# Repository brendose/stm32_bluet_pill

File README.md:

<h1 align="center">Welcome to Project: stm32_bluet_pill </br> (a Bluetooth OSHW design) </h1>
<div align="center">

<a href="#introduction">Introduction</a> &nbsp;&bull;&nbsp;
<a href="#directory">Directory</a> &nbsp;&bull;&nbsp;
<a href="#documentation">Documentation</a> &nbsp;&bull;&nbsp;
<a href="#notes">Notes</a>
</div>

# Introduction
The <b>stm32_bluet_pill</b> project is a 'breadboardable' 1.8V IO STM32WB55 Bluetooth Module with battery charging. 
The purpose of this project is to provide a development platform for wearables. The board contains:

- ST Microelectronics STM32WB55
- 32Mbit QSPI Flash
- Texas Instruments BQ25185 battery charger
- PCB Antenna with U.FL switch connector 
- 2x 15 pin GPIO headers
- Tag-Connect JTAG connector 
- USB-C connector
- 3-Pin Battery connector
- Charge Status and Bluetooth Connection indicator LEDs

## Directory

### Projects top-level directory

    .
    ├── bom                     # stm32_blue_pill iBOM
    ├── docs                    # Documentation files (alternatively `doc`)
    ├── images                  # Images used on this GitHub page
    ├── schematics              # Schematics of the stm32_bluet_pill
    ├── step                    # 3D STEP model of the design
    ├── tapeout                 # Gerbers, Drill Drawings and other output files for PCB Fab and Assembly
    └── README.md

## Documentation

### Block Diagram
<div align="center">

</div>

## Notes

This repository is not actively maintained, so if you spot any bugs, please <a href="https://github.com/brendose/stm32_bluet_pill/issues/new">raise an issue</a> and I will try get to it.

This is not an officially supported Google product.

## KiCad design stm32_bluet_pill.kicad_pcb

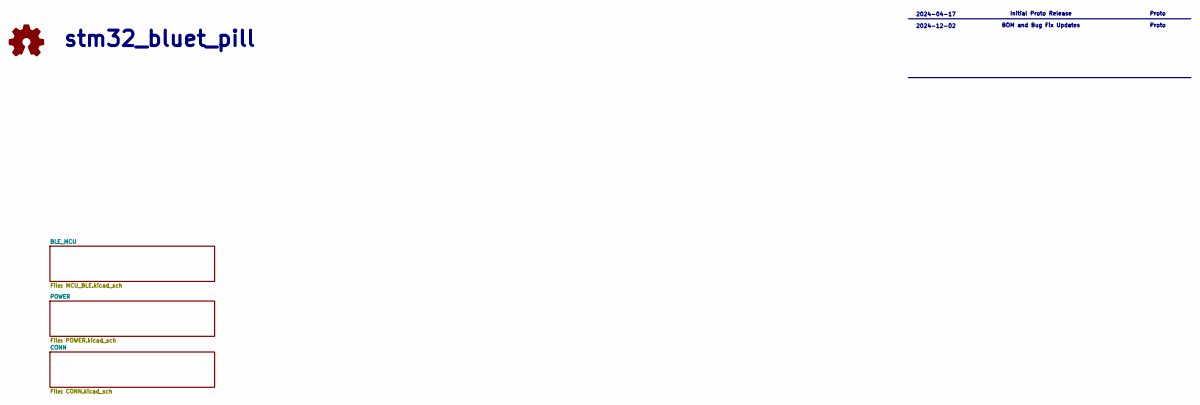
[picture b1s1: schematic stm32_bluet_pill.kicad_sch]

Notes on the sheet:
Proto
2024-04-17
${TITLE}
Initial Proto Release
BOM and Bug Fix Updates
2024-12-02

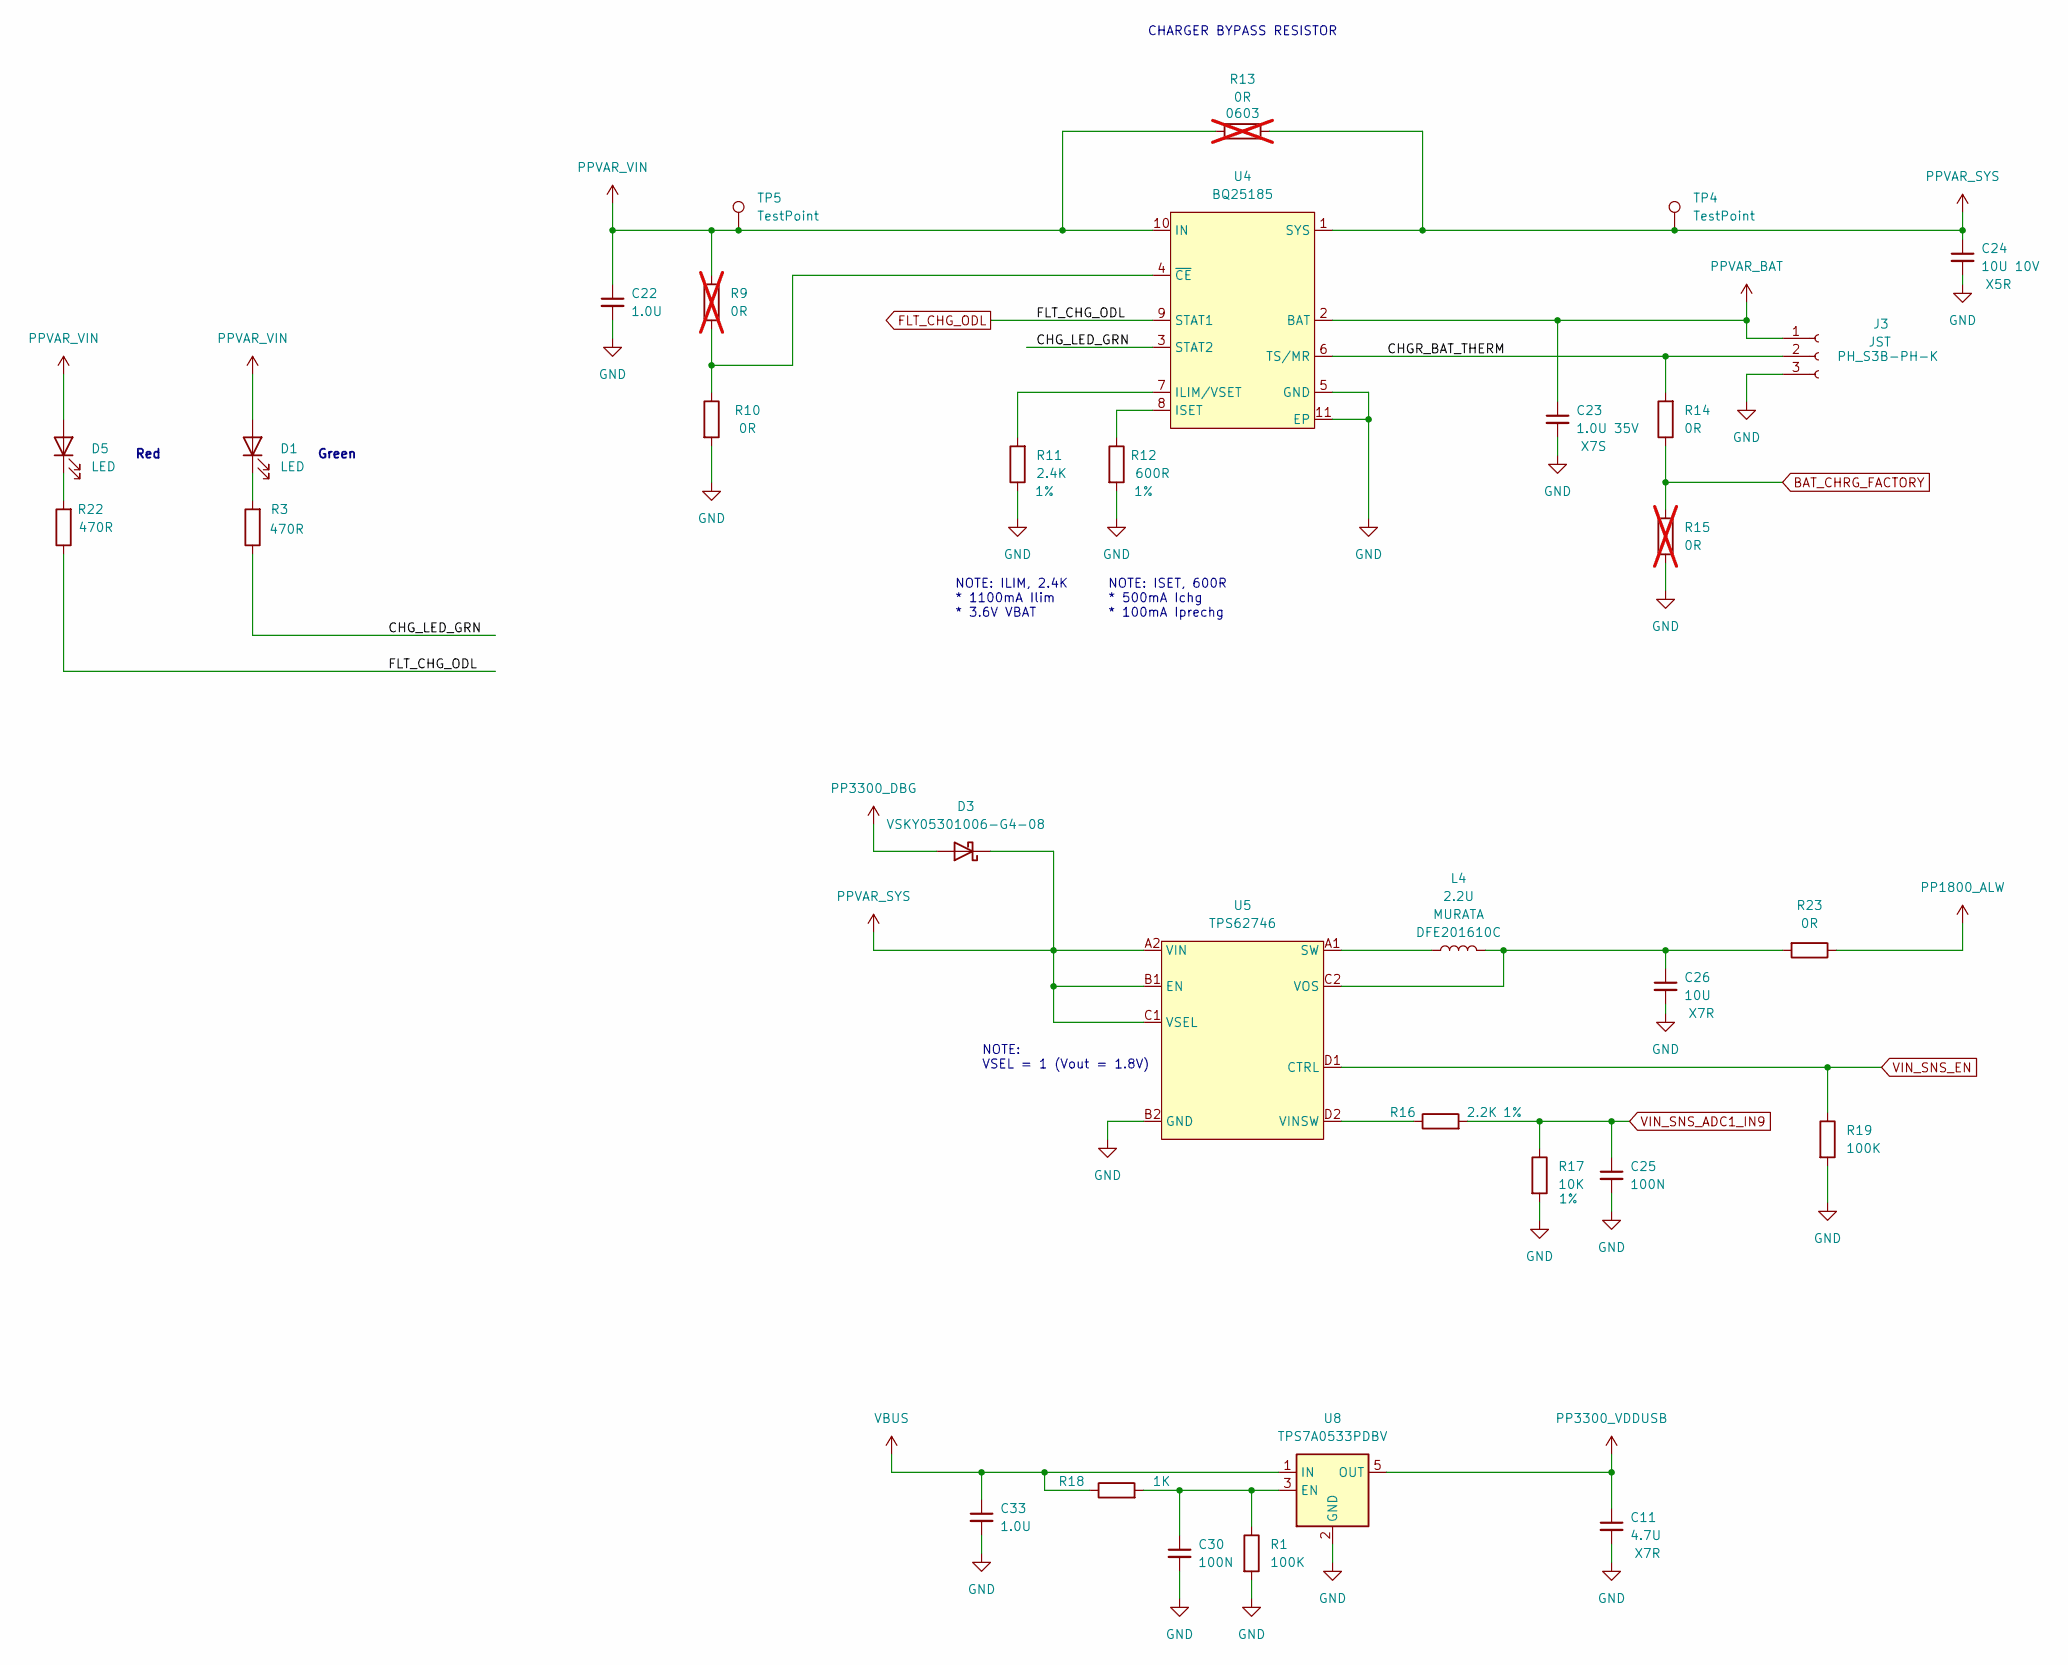
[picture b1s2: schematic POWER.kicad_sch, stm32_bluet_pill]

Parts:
C11: 4.7U; C_0402_1005Metric; MFG_PN GRM155R60J106ME11
C22, C33: 1.0U; C_0402_1005Metric
C23: 1.0U 35V; C_0402_1005Metric; MFR_PN C1005JB1V105K050BC
C24: 10U 10V; C_0402_1005Metric; MFR_PN CL05A106MP8NUB8
C25, C30: 100N; C_0201_0603Metric
C26: 10U; C_0402_1005Metric; MFG_PN GRM155R60J106ME11
D1, D5: LED; D_0402_1005Metric
D3: VSKY05301006-G4-08; D_0402_1005Metric
J3: PH_S3B-PH-K; JST_PH_S3B-PH-K_1x03_P2.00mm_Horizontal; MFG_PN PH_S3B-PH-K
L4: 2.2U; L_Murata_DFE201610P; MFG_PN DFE201610C
R1, R19: 100K; R_0201_0603Metric
R3, R22: 470R; R_0201_0603Metric
R9, R15: 0R; R_0201_0603Metric; not fitted
R10, R14: 0R; R_0201_0603Metric
R11: 2.4K; R_0201_0603Metric
R12: 600R; R_0201_0603Metric
R13: 0R; R_0603_1608Metric; not fitted
R16: 2.2K; R_0201_0603Metric
R17: 10K; R_0201_0603Metric
R18: 1K; R_0201_0603Metric
R23: 0R; R_0402_1005Metric
TP4, TP5: TestPoint; TestPoint_Pad_D1.0mm
U4: BQ25185; Texas_DLH_WSON-10
U5: TPS62746; Texas_DSBGA-8_0.705x1.468mm_Layout2x4_P0.4mm
U8: TPS7A0533PDBV; SOT-23-5

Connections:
/POWER/CHGR_BAT_THERM: J3.2, R14.2, U4.6 (TS/MR)
/POWER/CHG_LED_GRN: R3.1, U4.3 (STAT2)
BAT_CHRG_FACTORY: R14.1, R15.2; also elsewhere on the board
FLT_CHG_ODL: R22.1, U4.9 (STAT1); also elsewhere on the board
GND: C11.2, C22.2, C23.2, C24.2, C25.2, C26.2, C30.2, C33.2, J3.3, R1.2, R10.2, R11.1, R12.2, R15.1, R17.2, R19.2, U4.5 (GND), U4.11 (EP), U5.B2 (GND), U8.2 (GND); also elsewhere on the board
unnamed: D1.1 (K), R3.2
unnamed: D5.1 (K), R22.2
unnamed: R11.2, U4.7 (ILIM/VSET)
unnamed: R12.1, U4.8 (ISET)
unnamed: R9.1, R10.1, U4.4 (~CE)
unnamed: L4.1, U5.A1 (SW)
unnamed: R16.1, U5.D2 (VINSW)
unnamed: C26.1, L4.2, R23.2, U5.C2 (VOS)
unnamed: C30.1, R1.1, R18.2, U8.3 (EN)
PP1800_ALW: R23.1; also elsewhere on the board
PP3300_DBG: D3.2 (A); also elsewhere on the board
PP3300_VDDUSB: C11.1, U8.5 (OUT); also elsewhere on the board
PPVAR_BAT: C23.1, J3.1, U4.2 (BAT)
PPVAR_SYS: C24.1, D3.1 (K), R13.1, TP4.1, U4.1 (SYS), U5.A2 (VIN), U5.B1 (EN), U5.C1 (VSEL)
PPVAR_VIN: C22.1, D1.2 (A), D5.2 (A), R9.2, R13.2, TP5.1, U4.10 (IN); also elsewhere on the board
VBUS: C33.1, R18.1, U8.1 (IN); also elsewhere on the board
VIN_SNS_ADC1_IN9: C25.1, R16.2, R17.1; also elsewhere on the board
VIN_SNS_EN: R19.1, U5.D1 (CTRL); also elsewhere on the board

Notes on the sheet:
CHARGER BYPASS RESISTOR
NOTE: ILIM, 2.4K * 1100mA Ilim * 3.6V VBAT
NOTE: VSEL = 1 (Vout = 1.8V)
Red
NOTE: ISET, 600R * 500mA Ichg * 100mA Iprechg
Green

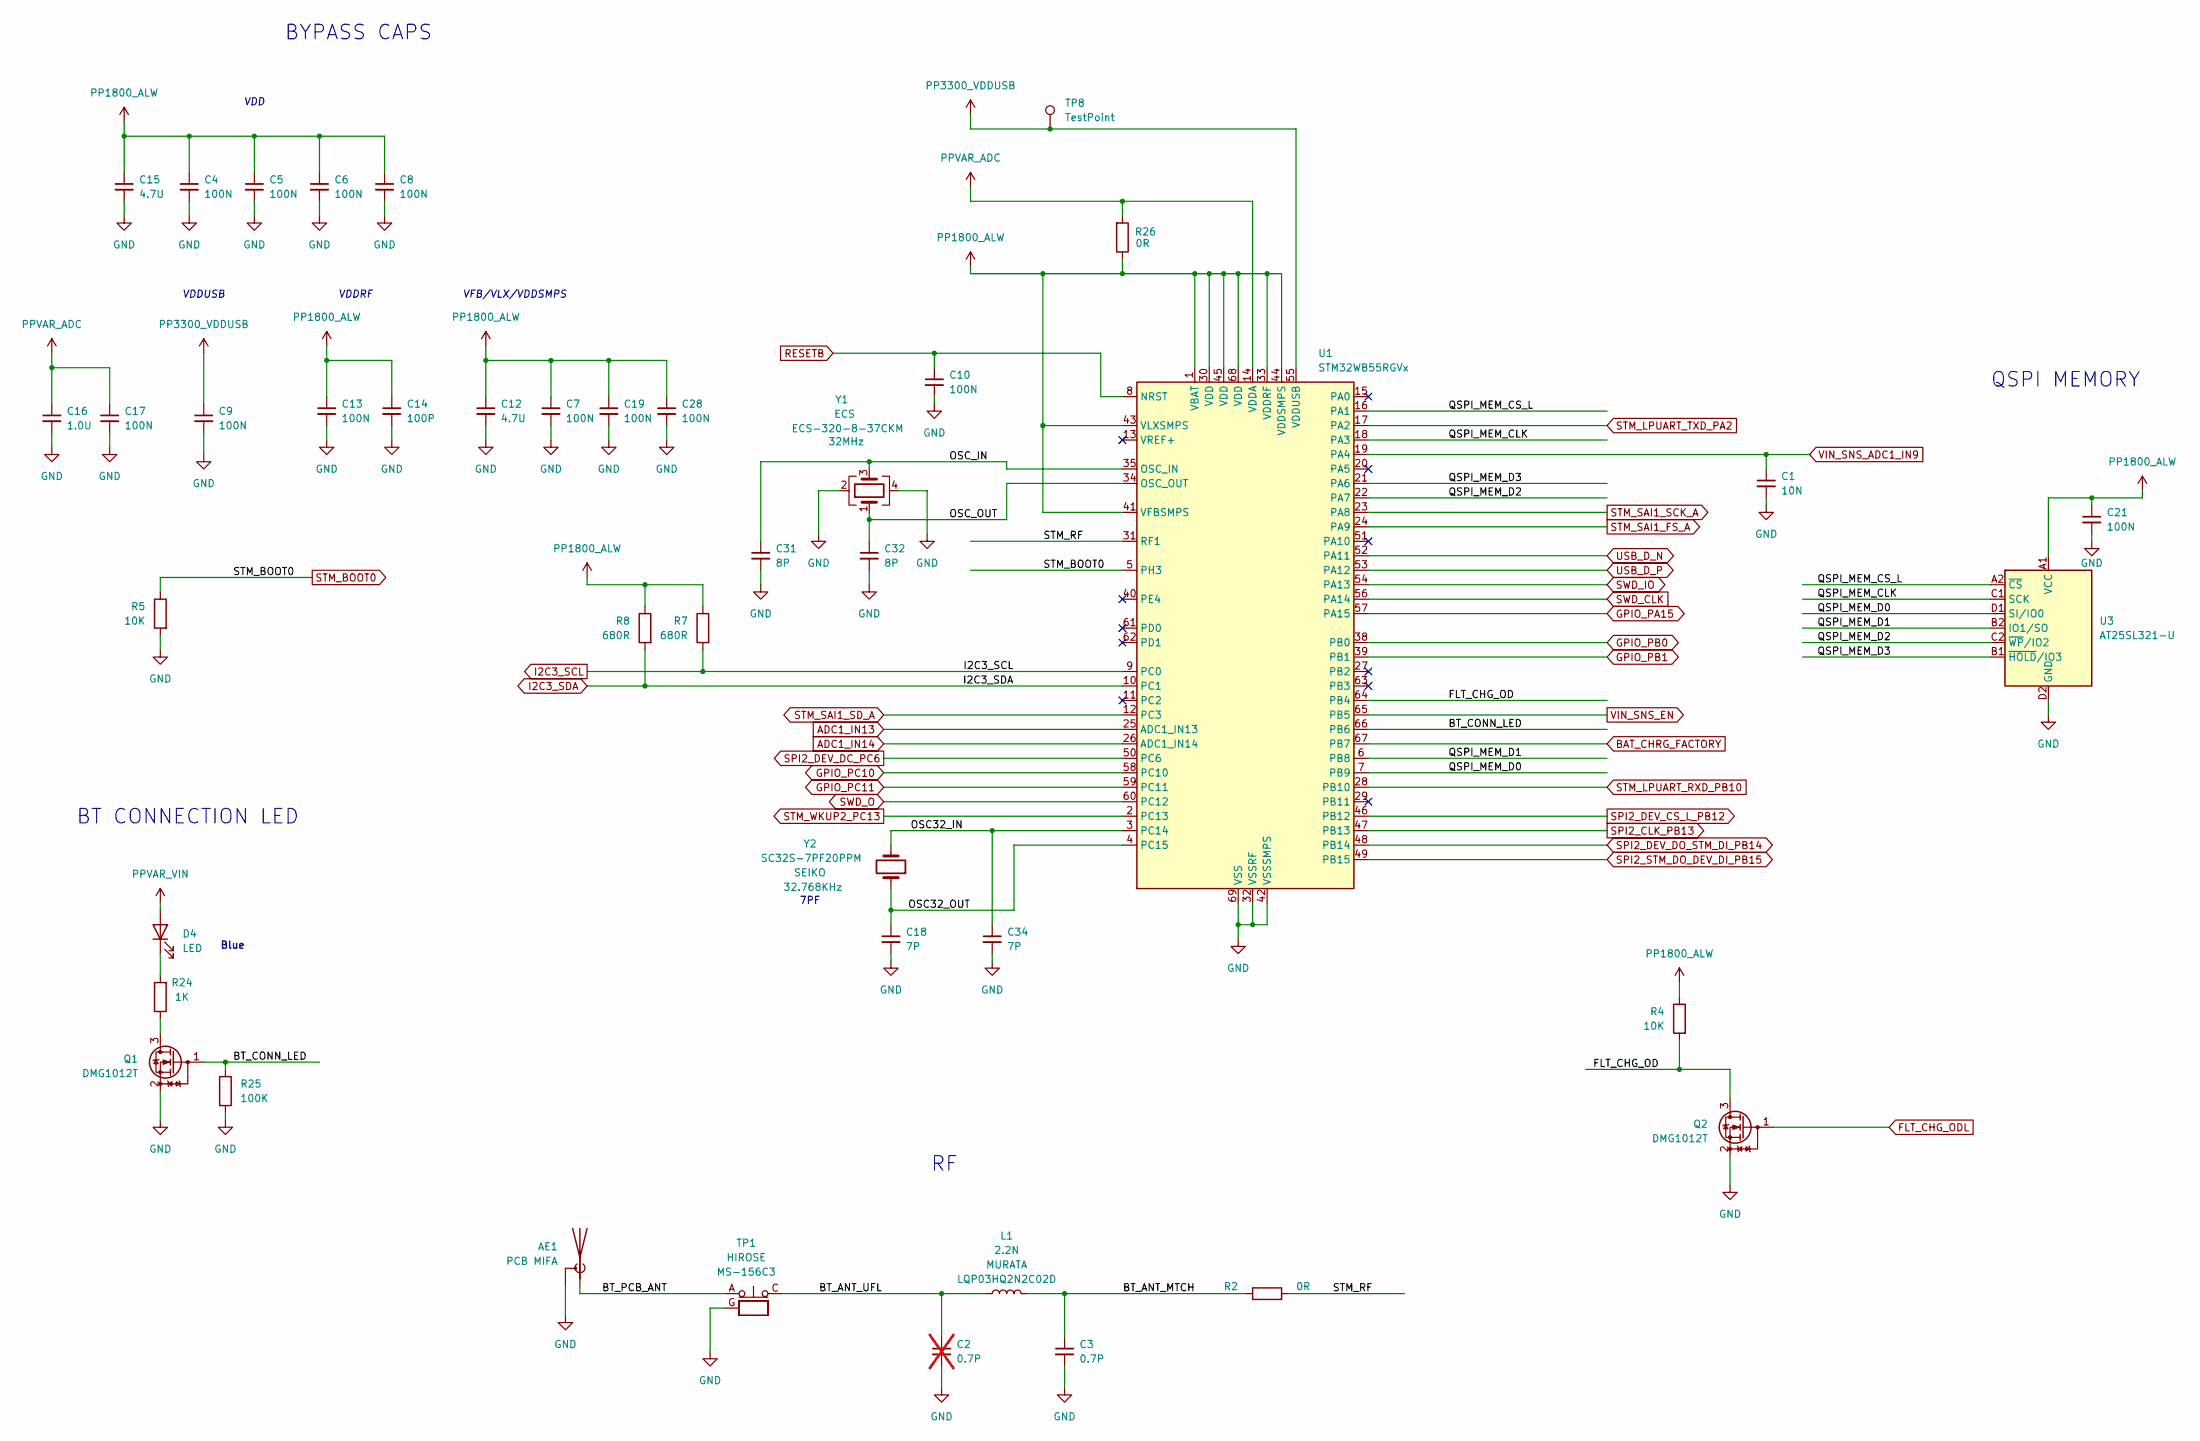
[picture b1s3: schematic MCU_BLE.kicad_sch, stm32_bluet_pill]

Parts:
AE1: PCB MIFA; Texas_SWRA117D_2.4GHz_Right
C1: 10N; C_0201_0603Metric
C2: 0.7P; C_0201_0603Metric; not fitted
C3: 0.7P; C_0201_0603Metric
C4, C5, C6, C7, C8, C9, C10, C13, C17, C19, C21, C28: 100N; C_0201_0603Metric
C12, C15: 4.7U; C_0402_1005Metric
C14: 100P; C_0201_0603Metric
C16: 1.0U; C_0201_0603Metric
C18, C34: 7P; C_0201_0603Metric
C31, C32: 8P; C_0201_0603Metric
D4: LED; D_0402_1005Metric
L1: 2.2N; D_0201_0603Metric; MFG_PN LQP03HQ2N2C02D
Q1, Q2: DMG1012T; SOT-523
R2: 0R; R_0201_0603Metric
R4, R5: 10K; R_0201_0603Metric
R7, R8: 680R; R_0201_0603Metric
R24: 1K; R_0201_0603Metric
R25: 100K; R_0201_0603Metric
R26: 0R; R_0402_1005Metric
TP1: MS-156C3; CoaxialSwitch_Hirose_MS-156C3_Horizontal; MFG_PN MS-156C3
TP8: TestPoint; TestPoint_Pad_D1.0mm
U1: STM32WB55RGVx; QFN-68-1EP_8x8mm_P0.4mm_EP6.4x6.4mm
U3: AT25SL321-U; WLCSP-8_1.551x2.284mm_P0.5mm
Y1: ECS-320-8-37CKM; Crystal_SMD_2016-4Pin_2.0x1.6mm; MFG_PN ECS-320-8-37CKM
Y2: SC32S-7PF20PPM; Crystal_SMD_3215-2Pin_3.2x1.5mm; MFG_PN SC32S-7PF20PPM

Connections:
/BLE_MCU/BT_ANT_MTCH: C3.1, L1.2, R2.1
/BLE_MCU/BT_ANT_UFL: C2.1, L1.1, TP1.C
/BLE_MCU/BT_CONN_LED: Q1.1 (G), R25.1, U1.66 (PB6)
/BLE_MCU/BT_PCB_ANT: AE1.1 (A), TP1.A
/BLE_MCU/FLT_CHG_OD: Q2.3 (D), R4.2, U1.64 (PB4)
/BLE_MCU/OSC32_IN: C34.1, U1.3 (PC14), Y2.2
/BLE_MCU/OSC32_OUT: C18.1, U1.4 (PC15), Y2.1
/BLE_MCU/OSC_IN: C31.1, U1.35 (OSC_IN), Y1.3
/BLE_MCU/OSC_OUT: C32.1, U1.34 (OSC_OUT), Y1.1
/BLE_MCU/QSPI_MEM_CLK: U1.18 (PA3), U3.C1 (SCK)
/BLE_MCU/QSPI_MEM_CS_L: U1.16 (PA1), U3.A2 (~CS)
/BLE_MCU/QSPI_MEM_D0: U1.7 (PB9), U3.D1 (SI/IO0)
/BLE_MCU/QSPI_MEM_D1: U1.6 (PB8), U3.B2 (IO1/SO)
/BLE_MCU/QSPI_MEM_D2: U1.22 (PA7), U3.C2 (~WP/IO2)
/BLE_MCU/QSPI_MEM_D3: U1.21 (PA6), U3.B1 (~HOLD/IO3)
/BLE_MCU/STM_RF: R2.2, U1.31 (RF1)
ADC1_IN13: U1.25 (ADC1_IN13); also elsewhere on the board
ADC1_IN14: U1.26 (ADC1_IN14); also elsewhere on the board
BAT_CHRG_FACTORY: U1.67 (PB7); also elsewhere on the board
FLT_CHG_ODL: Q2.1 (G); also elsewhere on the board
GND: AE1.2 (Shield), C1.2, C2.2, C3.2, C4.2, C5.2, C6.2, C7.2, C8.2, C9.2, C10.2, C12.2, C13.2, C14.2, C15.2, C16.2, C17.2, C18.2, C19.2, C21.2, C28.2, C31.2, C32.2, C34.2, Q1.2 (S), Q2.2 (S), R5.2, R25.2, TP1.G, U1.32 (VSSRF), U1.42 (VSSSMPS), U1.69 (VSS), U3.D2 (GND), Y1.2, Y1.4; also elsewhere on the board
GPIO_PA15: U1.57 (PA15); also elsewhere on the board
GPIO_PB0: U1.38 (PB0); also elsewhere on the board
GPIO_PB1: U1.39 (PB1); also elsewhere on the board
GPIO_PC10: U1.58 (PC10); also elsewhere on the board
GPIO_PC11: U1.59 (PC11); also elsewhere on the board
I2C3_SCL: R7.2, U1.9 (PC0); also elsewhere on the board
I2C3_SDA: R8.2, U1.10 (PC1); also elsewhere on the board
unnamed: D4.1 (K), R24.2
unnamed: Q1.3 (D), R24.1
PP1800_ALW: C4.1, C5.1, C6.1, C7.1, C8.1, C12.1, C13.1, C14.1, C15.1, C19.1, C21.1, C28.1, R4.1, R7.1, R8.1, R26.1, U1.1 (VBAT), U1.30 (VDD), U1.33 (VDDRF), U1.41 (VFBSMPS), U1.43 (VLXSMPS), U1.44 (VDDSMPS), U1.45 (VDD), U1.68 (VDD), U3.A1 (VCC); also elsewhere on the board
PP3300_VDDUSB: C9.1, TP8.1, U1.55 (VDDUSB); also elsewhere on the board
PPVAR_ADC: C16.1, C17.1, R26.2, U1.14 (VDDA); also elsewhere on the board
PPVAR_VIN: D4.2 (A); also elsewhere on the board
RESETB: C10.1, U1.8 (NRST); also elsewhere on the board
SPI2_CLK_PB13: U1.47 (PB13); also elsewhere on the board
SPI2_DEV_CS_L_PB12: U1.46 (PB12); also elsewhere on the board
SPI2_DEV_DC_PC6: U1.50 (PC6); also elsewhere on the board
SPI2_DEV_DO_STM_DI_PB14: U1.48 (PB14); also elsewhere on the board
SPI2_STM_DO_DEV_DI_PB15: U1.49 (PB15); also elsewhere on the board
STM_BOOT0: R5.1, U1.5 (PH3); also elsewhere on the board
STM_LPUART_RXD_PB10: U1.28 (PB10); also elsewhere on the board
STM_LPUART_TXD_PA2: U1.17 (PA2); also elsewhere on the board
STM_SAI1_FS_A: U1.24 (PA9); also elsewhere on the board
STM_SAI1_SCK_A: U1.23 (PA8); also elsewhere on the board
STM_SAI1_SD_A: U1.12 (PC3); also elsewhere on the board
STM_WKUP2_PC13: U1.2 (PC13); also elsewhere on the board
SWD_CLK: U1.56 (PA14); also elsewhere on the board
SWD_IO: U1.54 (PA13); also elsewhere on the board
SWD_O: U1.60 (PC12); also elsewhere on the board
USB_D_N: U1.52 (PA11); also elsewhere on the board
USB_D_P: U1.53 (PA12); also elsewhere on the board
VIN_SNS_ADC1_IN9: C1.1, U1.19 (PA4); also elsewhere on the board
VIN_SNS_EN: U1.65 (PB5); also elsewhere on the board

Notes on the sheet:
BT CONNECTION LED
QSPI MEMORY
BYPASS CAPS
7PF
VDDUSB
Blue
VDD
VFB/VLX/VDDSMPS
VDDRF

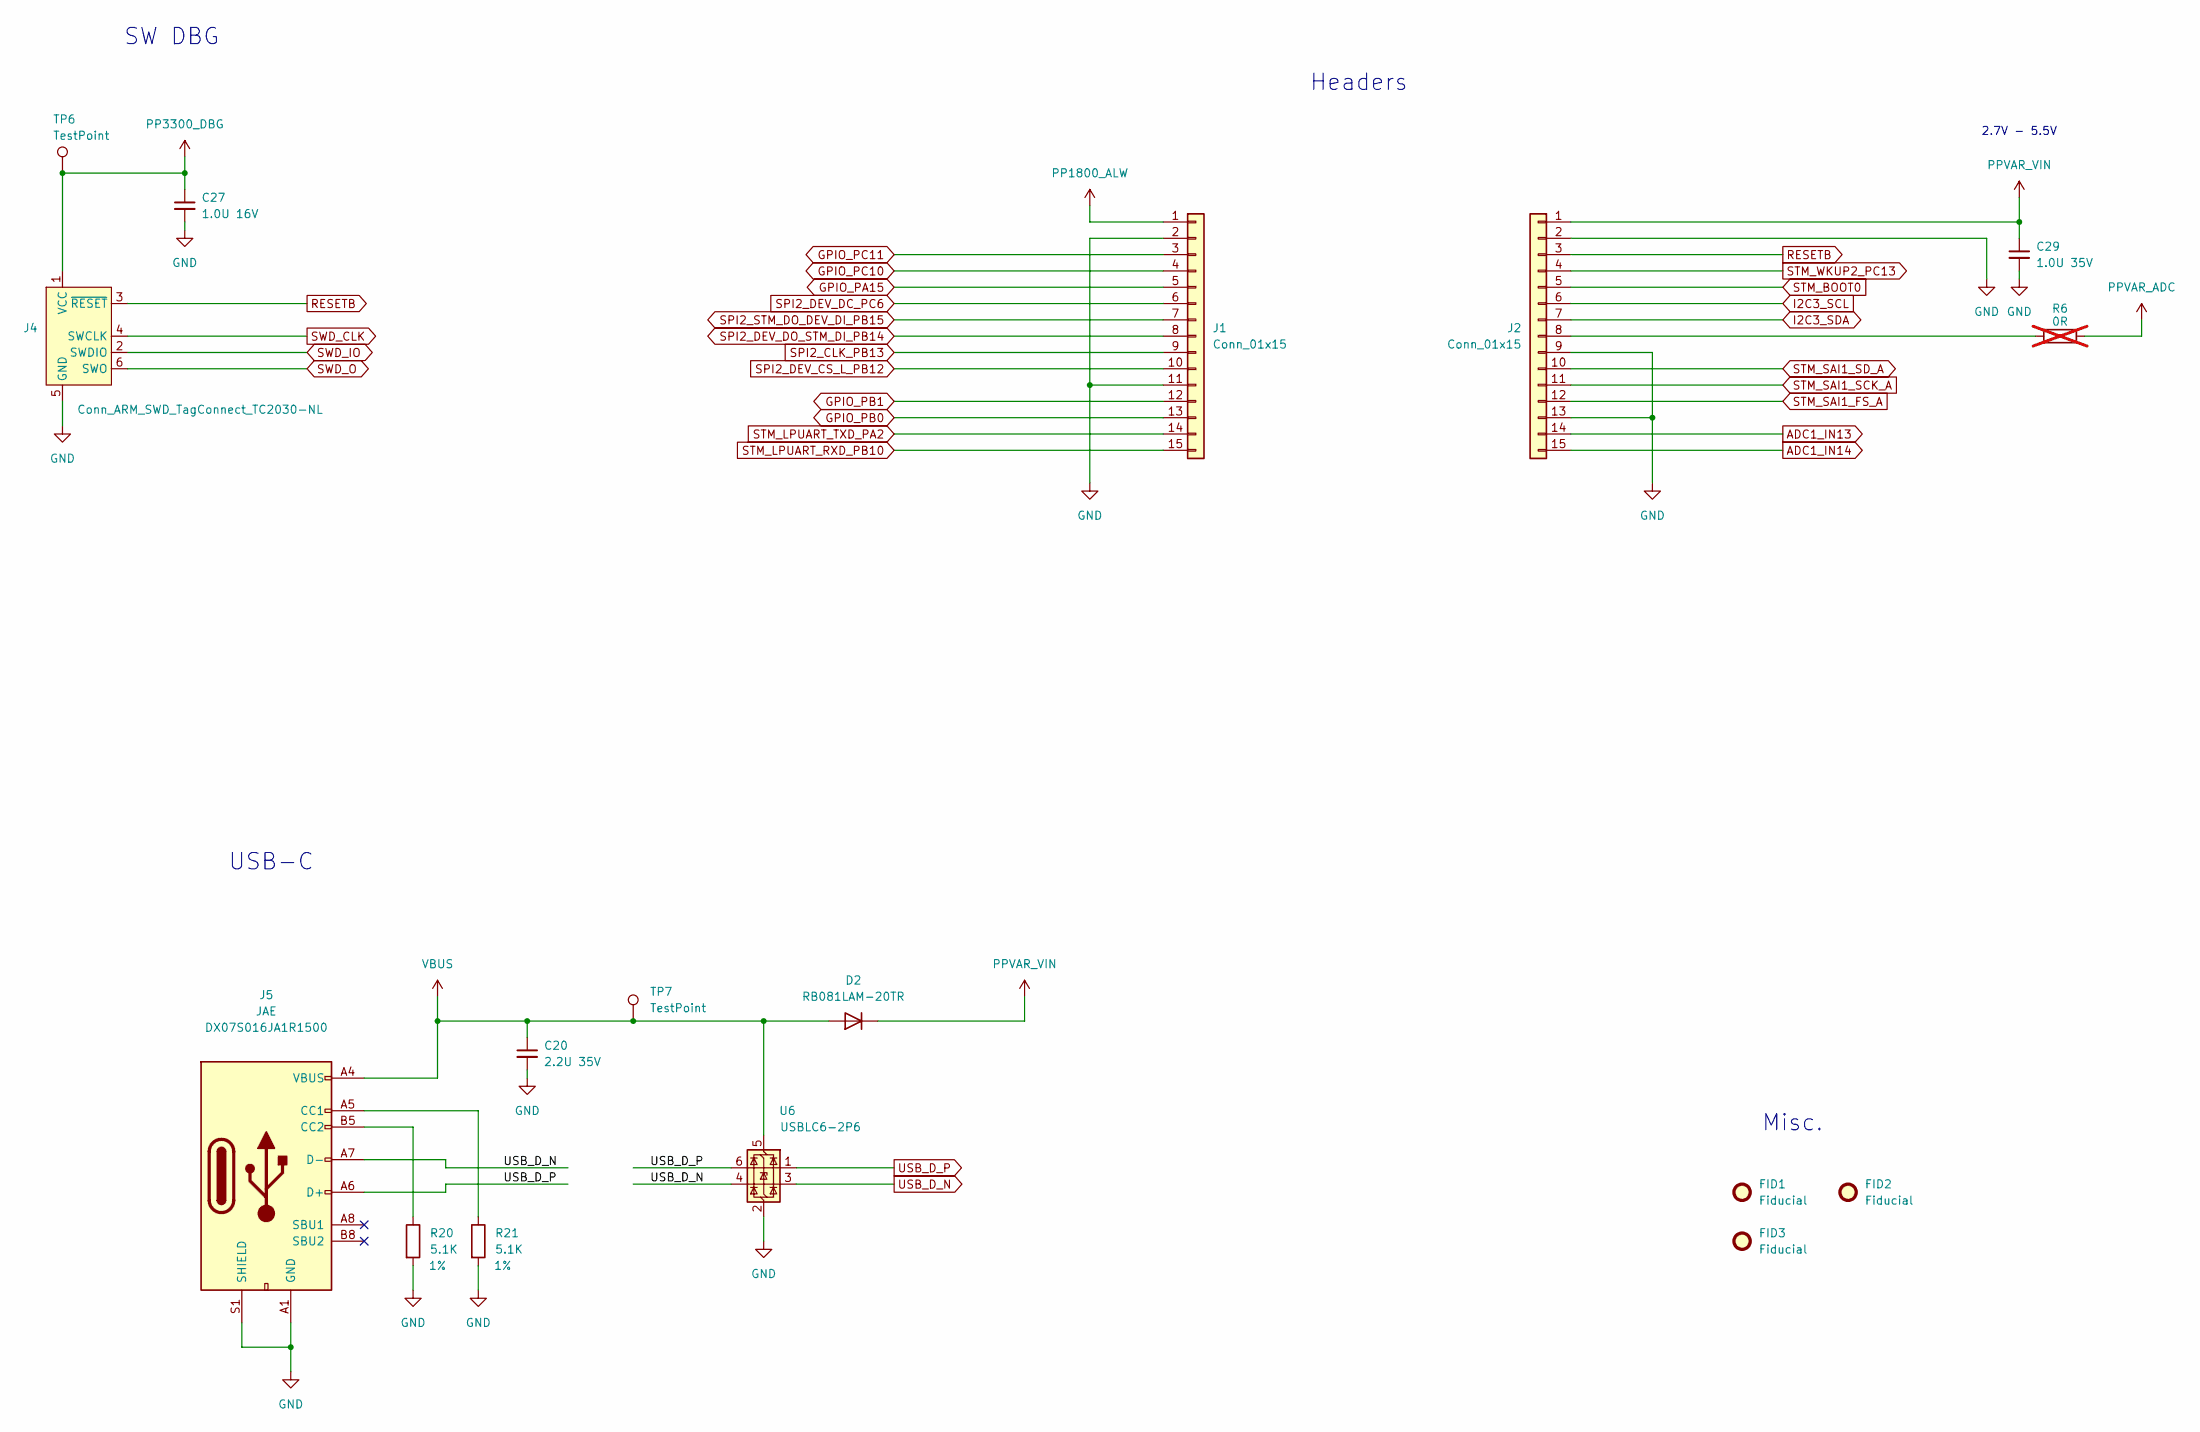
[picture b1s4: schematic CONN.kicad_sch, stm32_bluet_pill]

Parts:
C20: 2.2U 35V; C_0603_1608Metric
C27: 1.0U 16V; C_0402_1005Metric
C29: 1.0U 35V; C_0603_1608Metric
D2: RB081LAM-20TR; D_SOD-128
FID1, FID2, FID3: Fiducial; Fiducial_0.5mm_Mask1mm
J1, J2: Conn_01x15; PinHeader_1x15_P1.27mm_Vertical
J4: Conn_ARM_SWD_TagConnect_TC2030-NL; Tag-Connect_TC2030-IDC-NL_2x03_P1.27mm_Vertical
J5: DX07S016JA1R1500; USB_C_Receptacle_JAE_DX07S016JA1R1500; MFG_PN DX07S016JA1R1500
R6: 0R; R_0402_1005Metric; not fitted
R20, R21: 5.1K; R_0201_0603Metric
TP6, TP7: TestPoint; TestPoint_Pad_D1.0mm
U6: USBLC6-2P6; SOT-666

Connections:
ADC1_IN13: J2.14; also elsewhere on the board
ADC1_IN14: J2.15; also elsewhere on the board
GND: C20.2, C27.2, C29.2, J1.2, J1.11, J2.2, J2.9, J2.13, J4.5 (GND), J5.A1 (GND), J5.A12 (GND), J5.B1 (GND), J5.B12 (GND), J5.S1 (SHIELD), R20.2, R21.2, U6.2 (GND); also elsewhere on the board
GPIO_PA15: J1.5; also elsewhere on the board
GPIO_PB0: J1.13; also elsewhere on the board
GPIO_PB1: J1.12; also elsewhere on the board
GPIO_PC10: J1.4; also elsewhere on the board
GPIO_PC11: J1.3; also elsewhere on the board
I2C3_SCL: J2.6; also elsewhere on the board
I2C3_SDA: J2.7; also elsewhere on the board
unnamed: J2.8, R6.2
unnamed: J5.A5 (CC1), R21.1
unnamed: J5.B5 (CC2), R20.1
PP1800_ALW: J1.1; also elsewhere on the board
PP3300_DBG: C27.1, J4.1 (VCC), TP6.1; also elsewhere on the board
PPVAR_ADC: R6.1; also elsewhere on the board
PPVAR_VIN: C29.1, D2.1 (K), J2.1; also elsewhere on the board
RESETB: J2.3, J4.3 (~RESET); also elsewhere on the board
SPI2_CLK_PB13: J1.9; also elsewhere on the board
SPI2_DEV_CS_L_PB12: J1.10; also elsewhere on the board
SPI2_DEV_DC_PC6: J1.6; also elsewhere on the board
SPI2_DEV_DO_STM_DI_PB14: J1.8; also elsewhere on the board
SPI2_STM_DO_DEV_DI_PB15: J1.7; also elsewhere on the board
STM_BOOT0: J2.5; also elsewhere on the board
STM_LPUART_RXD_PB10: J1.15; also elsewhere on the board
STM_LPUART_TXD_PA2: J1.14; also elsewhere on the board
STM_SAI1_FS_A: J2.12; also elsewhere on the board
STM_SAI1_SCK_A: J2.11; also elsewhere on the board
STM_SAI1_SD_A: J2.10; also elsewhere on the board
STM_WKUP2_PC13: J2.4; also elsewhere on the board
SWD_CLK: J4.4 (SWCLK); also elsewhere on the board
SWD_IO: J4.2 (SWDIO); also elsewhere on the board
SWD_O: J4.6 (SWO); also elsewhere on the board
USB_D_N: J5.A7 (D-), J5.B7 (D-), U6.3 (I/O2), U6.4 (I/O2); also elsewhere on the board
USB_D_P: J5.A6 (D+), J5.B6 (D+), U6.1 (I/O1), U6.6 (I/O1); also elsewhere on the board
VBUS: C20.1, D2.2 (A), J5.A4 (VBUS), J5.A9 (VBUS), J5.B4 (VBUS), J5.B9 (VBUS), TP7.1, U6.5 (VBUS); also elsewhere on the board

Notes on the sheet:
Headers
USB-C
Misc.
SW DBG
2.7V - 5.5V

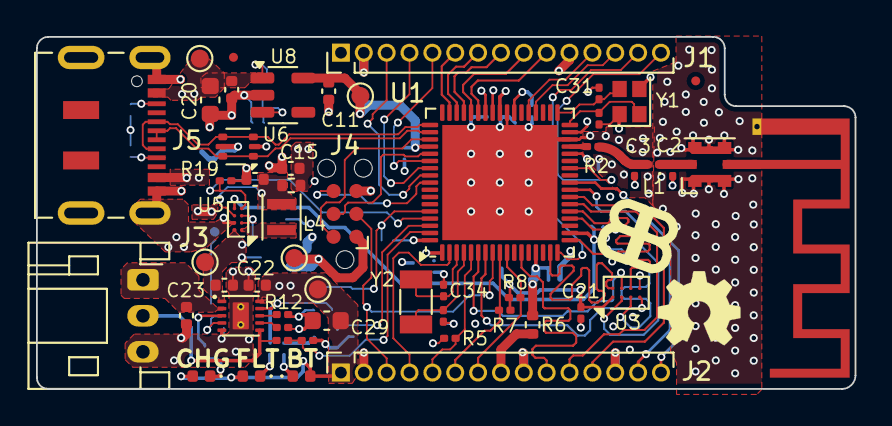
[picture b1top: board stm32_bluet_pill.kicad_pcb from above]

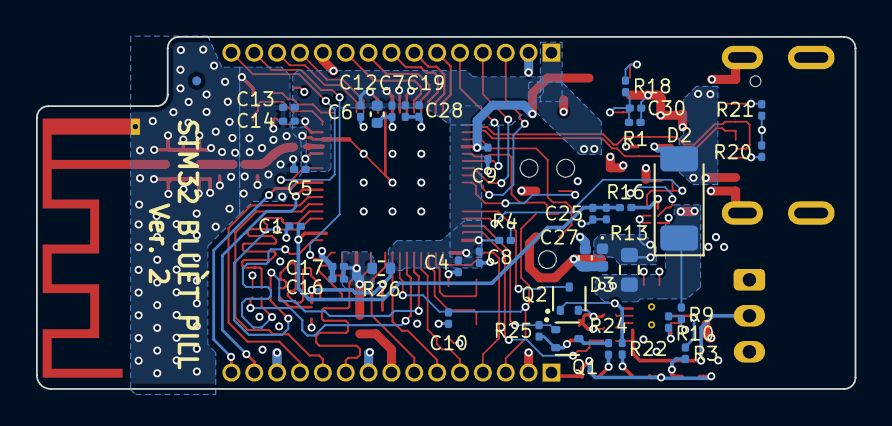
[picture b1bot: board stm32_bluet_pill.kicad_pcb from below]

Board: 4 copper layers, 45.5 x 19.6 mm, 92 parts (38 on the bottom side), 72 nets.

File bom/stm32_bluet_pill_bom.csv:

"Id";"Designator";"Footprint";"Quantity";"Designation";"Supplier and ref";
1;"R2,R14,R15,R10,R9";"R_0201_0603Metric";5;"0R";;;
2;"R5,R4,R17";"R_0201_0603Metric";3;"10K";;;
3;"C32,C31";"C_0201_0603Metric";2;"8P";;;
4;"C24,C15,C11,C23,C12";"C_0402_1005Metric";5;"4.7UF";;;
5;"U5";"Texas_DSBGA-8_0.705x1.468mm_Layout2x4_P0.4mm";1;"TPS62746";;;
6;"C29,C28";"C_0603_1608Metric";2;"4.7UF";;;
7;"C2,C3";"C_0201_0603Metric";2;"0.7PF";;;
8;"D1,D4,D5";"D_0402_1005Metric";3;"LED";;;
9;"R8,R7";"R_0201_0603Metric";2;"680R";;;
10;"R6";"R_0201_0603Metric";1;"22R";;;
11;"J1,J2";"PinHeader_1x15_P1.27mm_Vertical";2;"Conn_01x15";;;
12;"C26";"C_0402_1005Metric";1;"10UF";;;
13;"L1";"D_0201_0603Metric";1;"2.2NH";;;
14;"L4";"L_Murata_DFE201610P";1;"2.2UH";;;
15;"C21,C8,C6,C9,C13,C4,C17,C10,C7,C5,C25";"C_0201_0603Metric";11;"100NF";;;
16;"R23,R26";"R_0402_1005Metric";2;"0R";;;
17;"J3";"JST_PH_S3B-PH-K_1x03_P2.00mm_Horizontal";1;"BAT_SOCKET";;;
18;"U3";"WLCSP-8_1.551x2.284mm_P0.5mm";1;"AT25SL321-U";;;
19;"C34,C18";"C_0201_0603Metric";2;"7P";;;
20;"J5";"USB_C_Receptacle_JAE_DX07S016JA1R1500";1;"USB_C_Plug_USB2.0";;;
21;"R11";"R_0201_0603Metric";1;"2.4K";;;
22;"R12";"R_0201_0603Metric";1;"600R";;;
23;"Y1";"Crystal_SMD_2016-4Pin_2.0x1.6mm";1;"32MHz";;;
24;"TP1";"CoaxialSwitch_Hirose_MS-156C3_Horizontal";1;"MS-156C3";;;
25;"U4";"Texas_DLH_WSON-10";1;"BQ25185";;;
26;"Y2";"Crystal_SMD_3215-2Pin_3.2x1.5mm";1;"32.768k";;;
27;"U6";"SOT-666";1;"USBLC6-2P6";;;
28;"AE1";"Texas_SWRA117D_2.4GHz_Right";1;"Antenna_Shield";;;
29;"U8";"SOT-23-5";1;"TPS7A0533PDBV";;;
30;"C33,C22,C27";"C_0402_1005Metric";3;"1.0UF";;;
31;"R19,R1,R25";"R_0201_0603Metric";3;"100K";;;
32;"U1";"QFN-68-1EP_8x8mm_P0.4mm_EP6.4x6.4mm";1;"STM32WB55RGVx";;;
33;"C16";"C_0201_0603Metric";1;"1UF";;;
34;"C30";"C_0402_1005Metric";1;"100N";;;
35;"C14";"C_0201_0603Metric";1;"100PF";;;
36;"R20,R21";"R_0201_0603Metric";2;"5.1K";;;
37;"D3";"D_0402_1005Metric";1;"VSKY05301006-G4-08";;;
38;"Q1,Q2";"SOT-523";2;"DMG1012T";;;
39;"R24,R22,R3";"R_0201_0603Metric";3;"420R";;;
40;"R18";"R_0201_0603Metric";1;"1K";;;
41;"R13";"R_0603_1608Metric";1;"0R";;;
42;"R16";"R_0201_0603Metric";1;"2.2K";;;
43;"C1";"C_0201_0603Metric";1;"10NF";;;
44;"D2";"D_SOD-128";1;"RB081LAM-20TR";;;

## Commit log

2024-04-03 Add initial project files.
2024-04-04 Create tapeout directory
2024-04-04 Create README in tapeout directory
2024-04-04 Adding outputs, updated some component values.
2024-04-04 removed backup zips. adding updated output files
2024-04-05 Update README.md
    WIP - some work is TBD on README.mb
2024-04-05 Update README.md
    corrected title format
2024-04-06 updating design files
    updating schematics, gerbers, design files, etc.
2024-04-06 Update stm32_bluet_pill-block-diagram.png
    reduced the size of the block diagram
2024-04-16 renamed all 'Bluetooth_OSHW' files.
    renamed files to stm_32_bluet_pill to keep consistency with the public git repo name.
2024-04-16 removing unnecessary files
2024-04-18 Updated project
    - Changed board stackup, trace-widths
    - Changed VIA size
    - Fixed fab drawings
    - added CHG FLT LED
    - Removed unnecessary files
2024-04-18 Update stm32_bluet_pill.png
    cropped main image
2024-04-24 Update README.md
    Added disclaimer at the bottom.
2024-12-03 Various BOM and Bug Fixes * Changed Stackup to common JLCPCB stackup * Modified trace widths as per new stackup * Reduced drill hole size * Rotated uFL connector as per datasheet pinout * Added pop o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
